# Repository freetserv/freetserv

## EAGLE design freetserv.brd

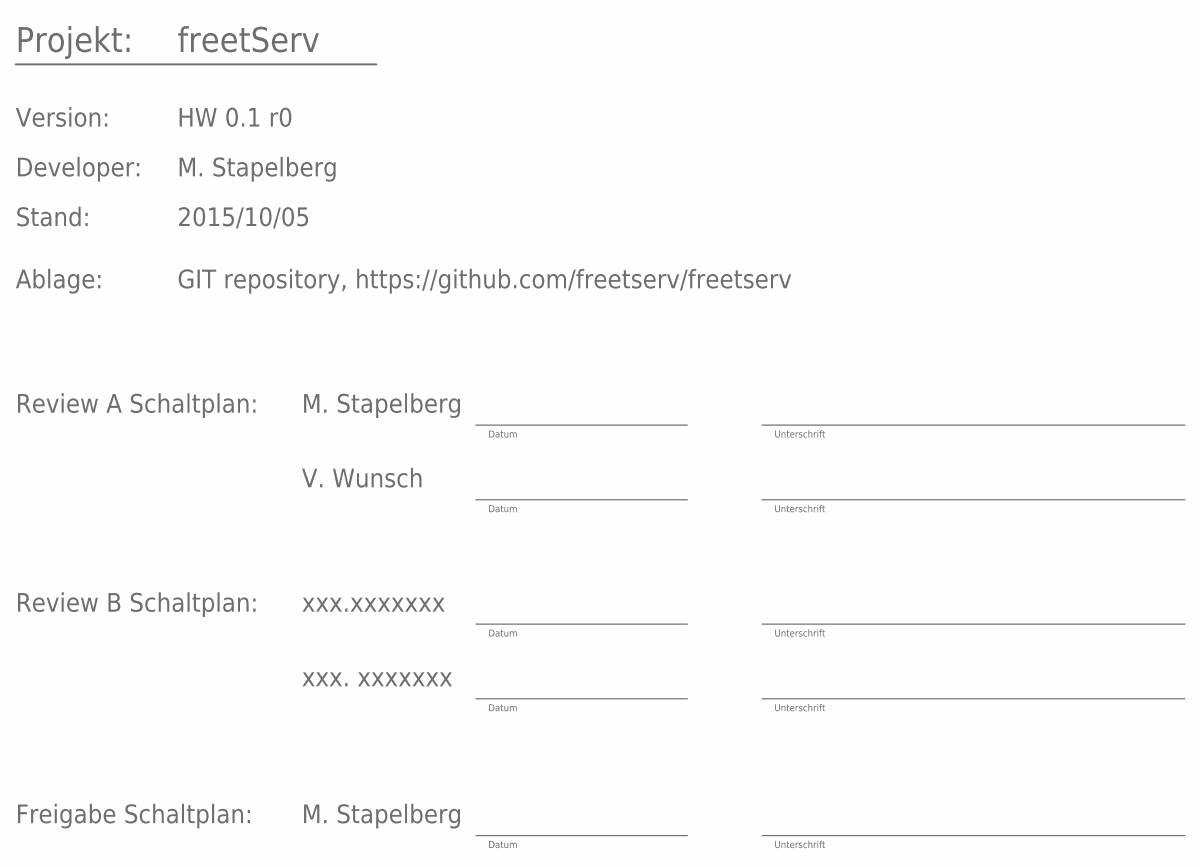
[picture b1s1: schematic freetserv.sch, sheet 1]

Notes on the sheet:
freetServ
Projekt:
Version:
HW 0.1 r0
Developer:
M. Stapelberg
Stand:
2015/10/05
Review A Schaltplan:
Datum
Unterschrift
V. Wunsch
Freigabe Schaltplan:
Ablage:
GIT repository, https://github.com/freetserv/freetserv
Review B Schaltplan:
xxx.xxxxxxx
xxx. xxxxxxx

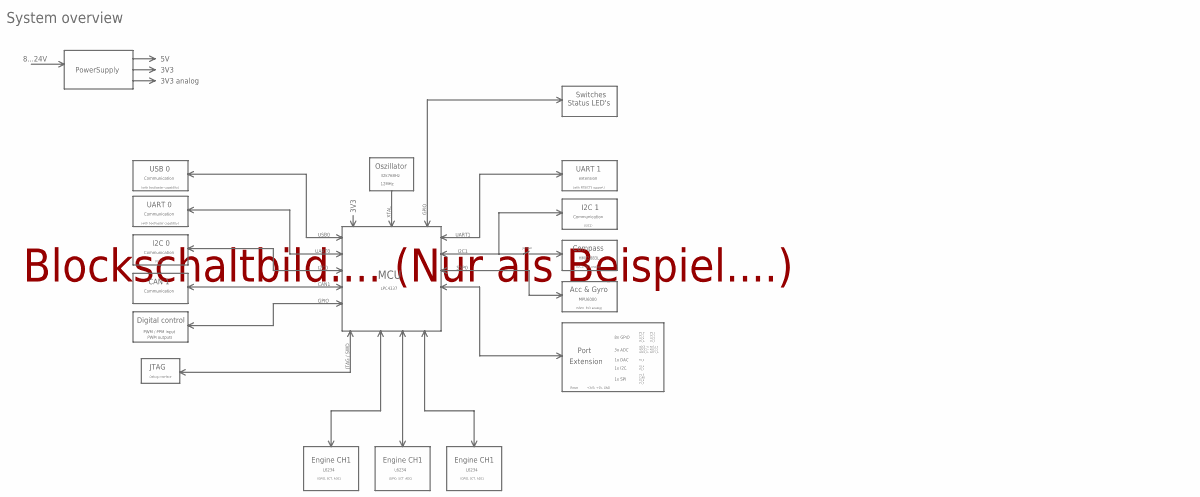
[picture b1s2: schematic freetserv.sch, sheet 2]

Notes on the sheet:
System overview
MCU
PowerSupply
3V3
3V3 analog
8...24V
JTAG
PWM / PPM input
PWM outputs
Digital control
Communication
CAN 1
I2C 0
UART 0
USB 0
(with bootloader capability)
Debug interface
I2C 1
UART 1
extension
(with RTS/CTS support)
8x GPIO
Port
Extension
3x ADC
1x DAC
1x I2C
1x SPI
Reset
+3V3, +5V, GND
(I2C0)
HMC5883L
Compass
Jumper
I2C1
UART1
UART0
USB0
I2C0
(I2C1)

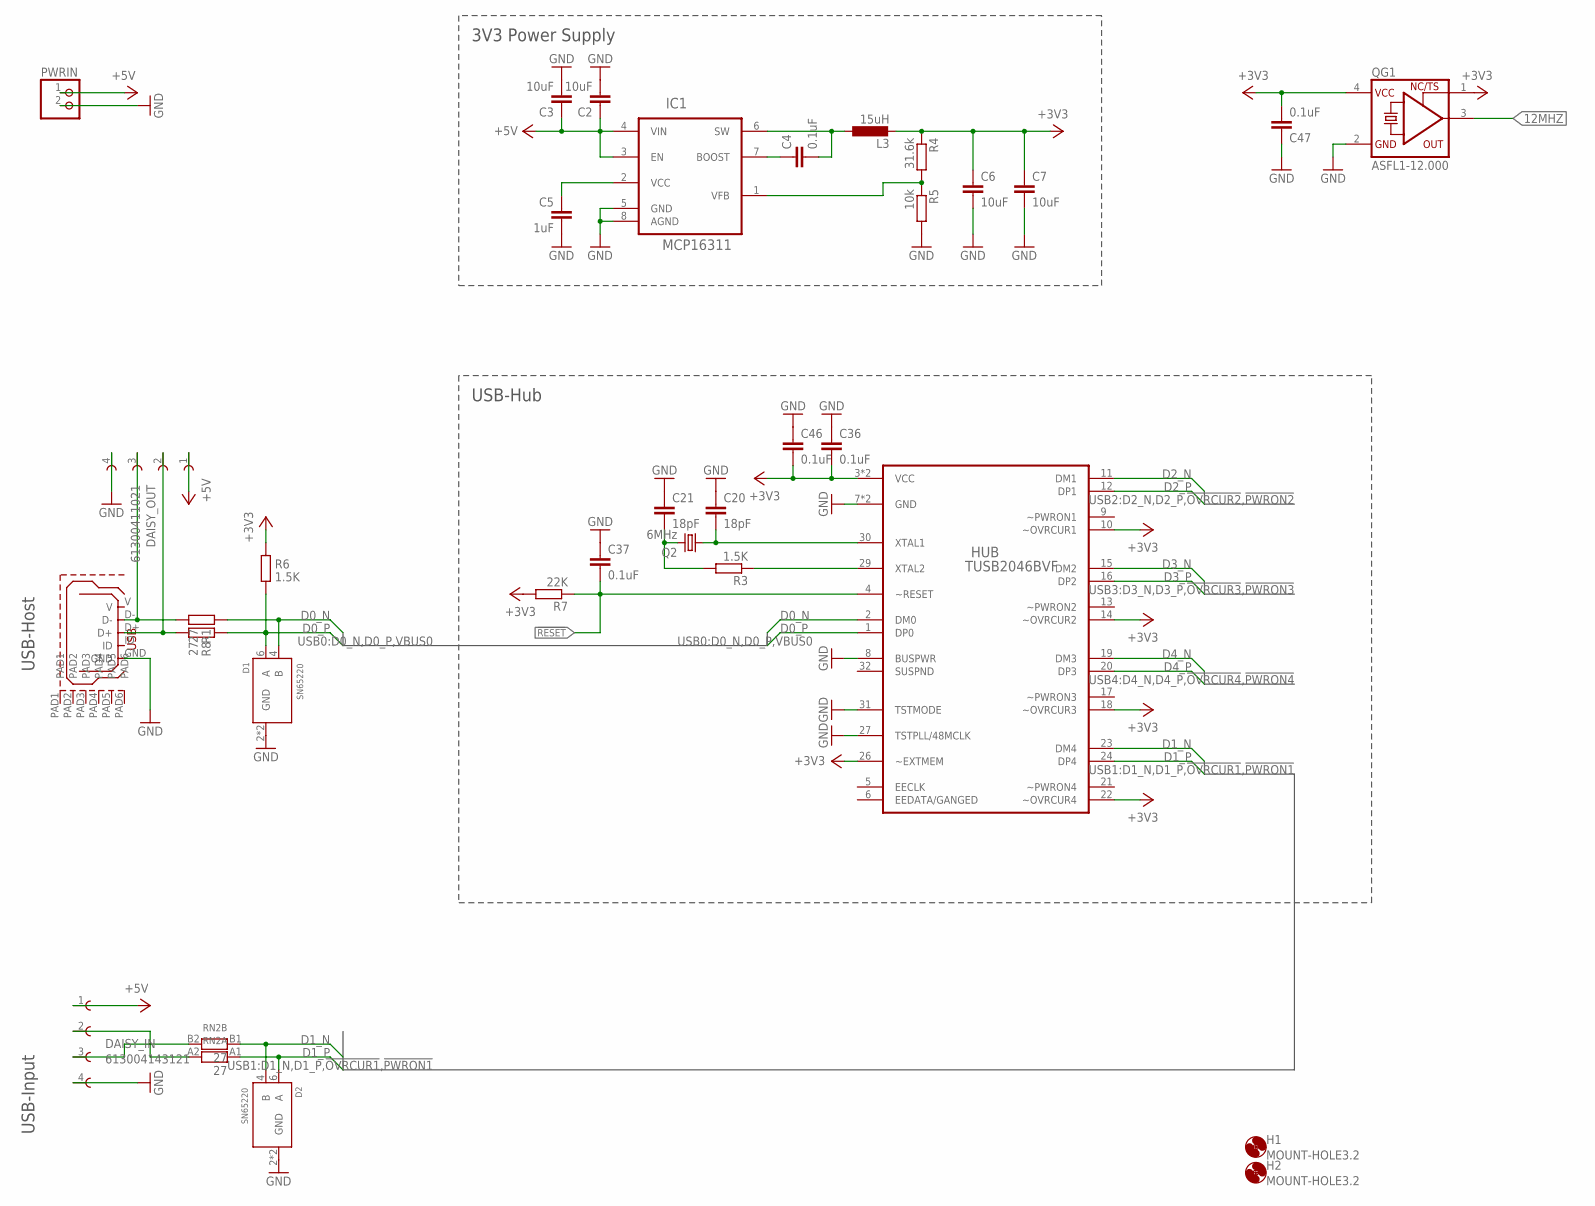
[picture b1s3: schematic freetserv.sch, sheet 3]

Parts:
C2, C3, C6, C7: 10uF; C0805; PARTNO 490-10517-1-ND
C4, C36, C37, C46, C47: 0.1uF; C0805; PARTNO 1276-1003-1-ND
C5: 1uF; C0805; PARTNO 311-1365-1-ND
C20, C21: 18pF; C0805; PARTNO 709-1171-1-ND
D1, D2: SN65220; SOT23-6; PARTNO 296-9694-1-ND
DAISY_IN: 613004143121; PARTNO 732-2863-ND
DAISY_OUT: 61300411021; PARTNO 732-5337-ND
H1, H2: MOUNT-HOLE3.2; 3,2
HUB: TUSB2046BVF; QFP80P900X900X145-32N
IC1: MCP16311; MSOP8; PARTNO MCP16311-E/MS-ND
L3: 15uH; NR60XX; PARTNO 587-2624-1-ND
PWRIN: PINHD-1X2; 1X02; PARTNO A1921-ND
Q2: 6MHz; CSM-7X-DU; PARTNO 535-10208-1-ND
QG1: ASFL1-12.000; XO53; PARTNO 535-9253-1-ND
R1, R8: 27; R0805; PARTNO 311-27ARCT-ND
R3, R6: 1.5K; R0805; PARTNO 311-1.5KARCT-ND
R4: 31.6k; R0805; PARTNO 311-31.6KCRCT-ND
R5: 10k; R0805; PARTNO 311-10KARCT-ND
R7: 22K; R0805; PARTNO 311-22KARCT-ND
RN2: 27; EXBV4V; PARTNO Y2270CT-ND
USB_HOST: USB_MICROB; USB_MICROB_PACKAGE; PARTNO H11634CT-ND

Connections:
12MHZ: QG1.3 (OUT); also elsewhere on the board
!RESET: C37.2, HUB.4 (~RESET), R7.1; also elsewhere on the board
+3V3: C6.1, C7.1, C36.2, C46.2, C47.2, HUB.3 (VCC), HUB.10 (~OVRCUR1), HUB.14 (~OVRCUR2), HUB.18 (~OVRCUR3), HUB.22 (~OVRCUR4), HUB.25 (VCC), HUB.26 (~EXTMEM), L3.2, QG1.1 (TS), QG1.4 (VCC), R4.1, R6.1, R7.2; also elsewhere on the board
+5V: C2.1, C3.1, DAISY_IN.1, DAISY_OUT.1, IC1.3 (EN), IC1.4 (VIN), PWRIN.1
D0_N: D1.4 (B), HUB.2 (DM0), R1.1
D0_P: D1.6 (A), HUB.1 (DP0), R6.2, R8.1
D1_N: D2.4 (B), HUB.23 (DM4), RN2.B1 (1)
D1_P: D2.6 (A), HUB.24 (DP4), RN2.A1 (1)
D2_N: HUB.11 (DM1); also elsewhere on the board
D2_P: HUB.12 (DP1); also elsewhere on the board
D3_N: HUB.15 (DM2); also elsewhere on the board
D3_P: HUB.16 (DP2); also elsewhere on the board
D4_N: HUB.19 (DM3); also elsewhere on the board
D4_P: HUB.20 (DP3); also elsewhere on the board
DX0_N: DAISY_OUT.3, R1.2, USB_HOST.D-
DX0_P: DAISY_OUT.2, R8.2, USB_HOST.D+
GND: C2.2, C3.2, C5.2, C6.2, C7.2, C20.1, C21.1, C36.1, C37.1, C46.1, C47.1, D1.2 (GND), D1.5 (GND), D2.2 (GND), D2.5 (GND), DAISY_IN.4, DAISY_OUT.4, HUB.7 (GND), HUB.8 (BUSPWR), HUB.27 (TSTPLL/48MCLK), HUB.28 (GND), HUB.31 (TSTMODE), IC1.5 (GND), IC1.8 (AGND), PWRIN.2, QG1.2 (GND), R5.2, USB_HOST.GND; also elsewhere on the board
unnamed: C4.1, IC1.7 (BOOST)
unnamed: C4.2, IC1.6 (SW), L3.1
unnamed: IC1.1 (VFB), R4.2, R5.1
unnamed: DAISY_IN.2, RN2.A2 (2)
unnamed: DAISY_IN.3, RN2.B2 (2)
unnamed: C5.1, IC1.2 (VCC)
unnamed: HUB.29 (XTAL2), R3.1
unnamed: C20.2, HUB.30 (XTAL1), Q2.1
unnamed: C21.2, Q2.2, R3.2

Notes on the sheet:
3V3 Power Supply
USB-Hub
USB-Input
USB-Host

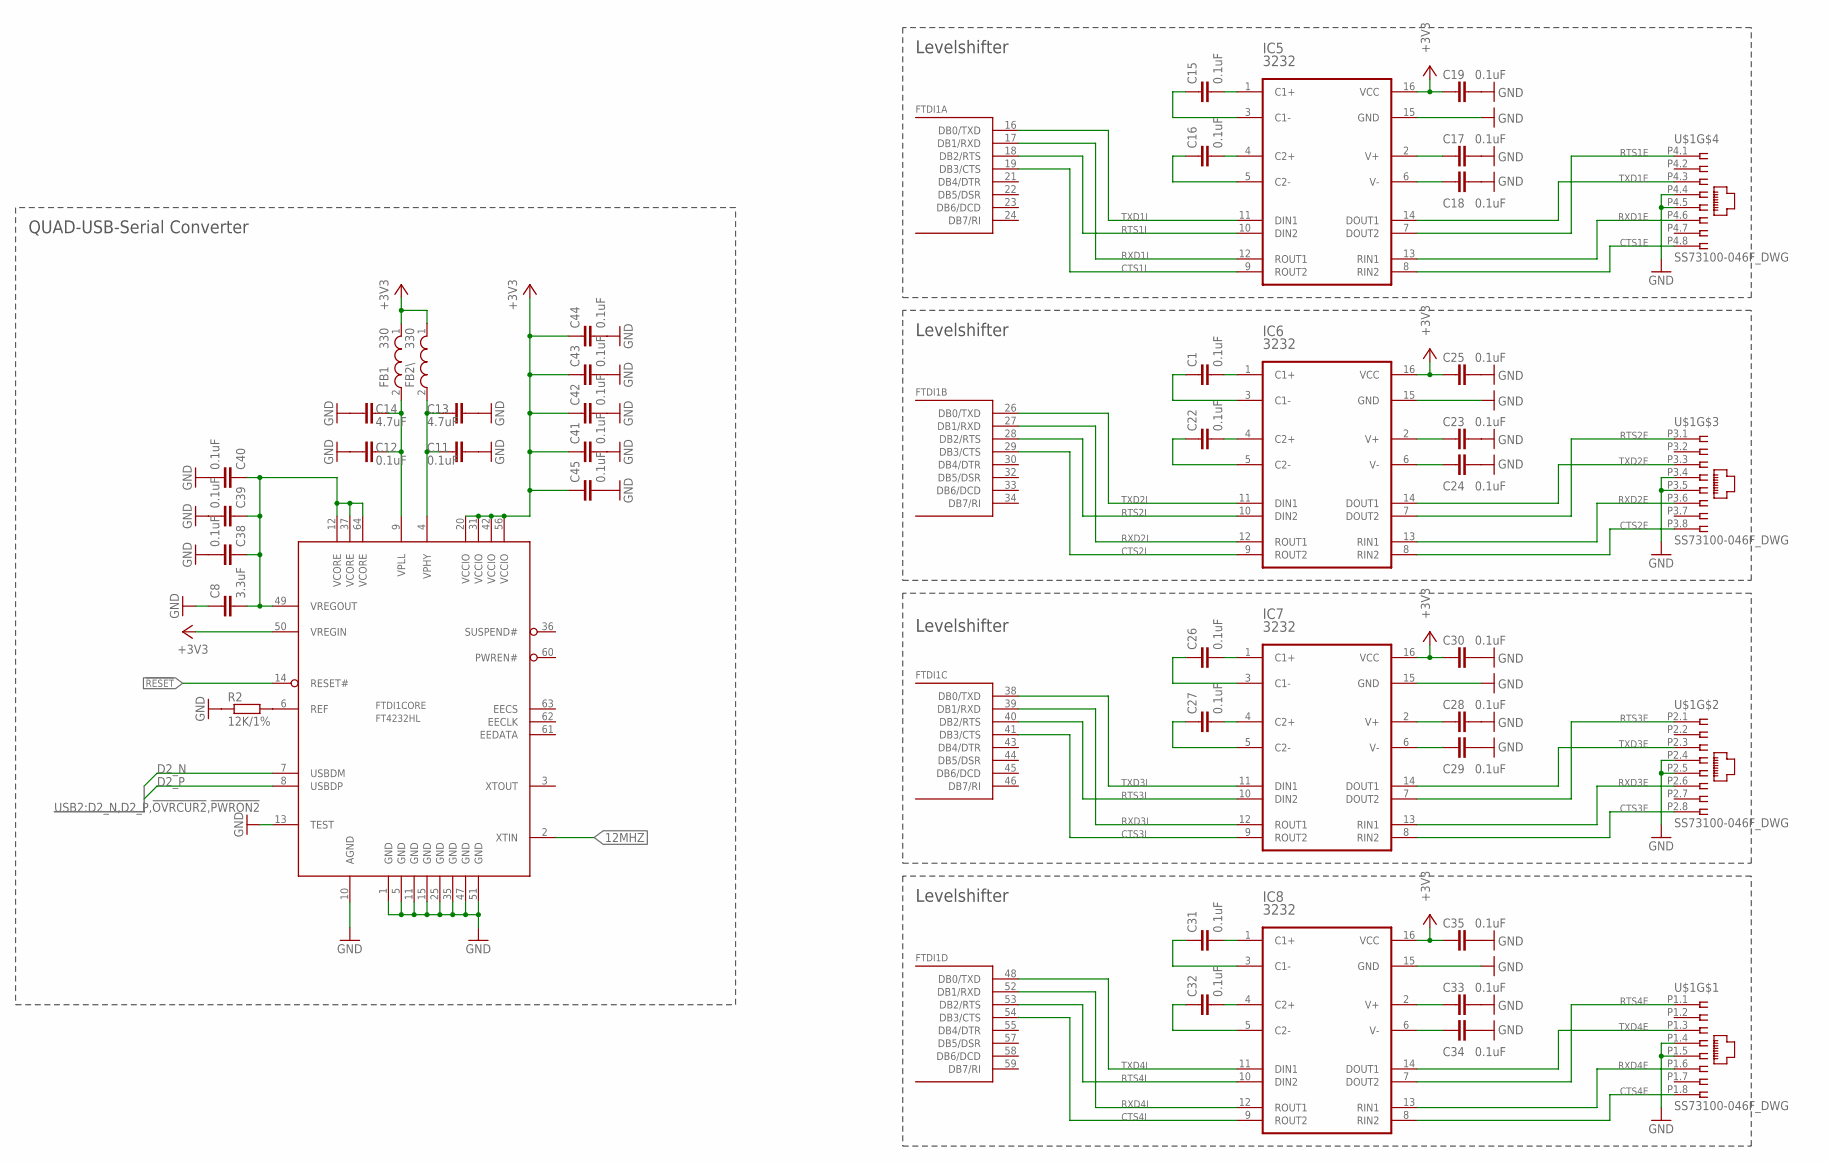
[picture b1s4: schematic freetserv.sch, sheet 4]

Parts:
C1, C11, C12, C15, C16, C17, C18, C19, C22, C23, C24, C25, C26, C27, C28, C29, C30, C31, C32, C33, C34, C35, C38, C39, C40, C41, C42, C43, C44, C45: 0.1uF; C0805; PARTNO 1276-1003-1-ND
C8: 3.3uF; C0805; PARTNO 445-7589-1-ND
C13, C14: 4.7uF; C0805; PARTNO 1276-2972-1-ND
FB1, FB2\: 330; WE-KI_0805A; PARTNO 490-5988-1-ND
FTDI1: FT4232HL; LQFP64; PARTNO 768-1026-1-ND
IC5, IC6, IC7, IC8: 3232; SOP65P640X120-16N; PARTNO 296-19263-1-ND
R2: 12K/1%; R0805; PARTNO 311-12.0KCRCT-ND
U$1: SS73100-046F_DWG; SS73100-046F; PARTNO 380-1225-ND

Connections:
12MHZ: FTDI1.2 (XTIN); also elsewhere on the board
!RESET: FTDI1.14 (RESET#); also elsewhere on the board
+1V8-1: C8.2, C38.1, C39.1, C40.1, FTDI1.12 (VCORE), FTDI1.37 (VCORE), FTDI1.49 (VREGOUT), FTDI1.64 (VCORE)
+3V3: C19.2, C25.2, C30.2, C35.2, C41.1, C42.1, C43.1, C44.1, C45.1, FB1.1, FB2\.1, FTDI1.20 (VCCIO), FTDI1.31 (VCCIO), FTDI1.42 (VCCIO), FTDI1.50 (VREGIN), FTDI1.56 (VCCIO), IC5.16 (VCC), IC6.16 (VCC), IC7.16 (VCC), IC8.16 (VCC); also elsewhere on the board
CTS1E: IC5.8 (RIN2), U$1.P4.8 (8)
CTS1I: FTDI1.19 (DB3/CTS), IC5.9 (ROUT2)
CTS2E: IC6.8 (RIN2), U$1.P3.8 (8)
CTS2I: FTDI1.29 (DB3/CTS), IC6.9 (ROUT2)
CTS3E: IC7.8 (RIN2), U$1.P2.8 (8)
CTS3I: FTDI1.41 (DB3/CTS), IC7.9 (ROUT2)
CTS4E: IC8.8 (RIN2), U$1.P1.8 (8)
CTS4I: FTDI1.54 (DB3/CTS), IC8.9 (ROUT2)
D2_N: FTDI1.7 (USBDM); also elsewhere on the board
D2_P: FTDI1.8 (USBDP); also elsewhere on the board
GND: C8.1, C11.2, C12.2, C13.2, C14.2, C17.1, C18.1, C19.1, C23.1, C24.1, C25.1, C28.1, C29.1, C30.1, C33.1, C34.1, C35.1, C38.2, C39.2, C40.2, C41.2, C42.2, C43.2, C44.2, C45.2, FTDI1.1 (GND), FTDI1.5 (GND), FTDI1.10 (AGND), FTDI1.11 (GND), FTDI1.13 (TEST), FTDI1.15 (GND), FTDI1.25 (GND), FTDI1.35 (GND), FTDI1.47 (GND), FTDI1.51 (GND), IC5.15 (GND), IC6.15 (GND), IC7.15 (GND), IC8.15 (GND), R2.1, U$1.P1.4 (4), U$1.P1.5 (5), U$1.P2.4 (4), U$1.P2.5 (5), U$1.P3.4 (4), U$1.P3.5 (5), U$1.P4.4 (4), U$1.P4.5 (5); also elsewhere on the board
unnamed: C1.2, IC6.1 (C1+)
unnamed: C1.1, IC6.3 (C1-)
unnamed: C22.2, IC6.4 (C2+)
unnamed: C22.1, IC6.5 (C2-)
unnamed: FTDI1.6 (REF), R2.2
unnamed: C11.1, C13.1, FB2\.2, FTDI1.4 (VPHY)
unnamed: C12.1, C14.1, FB1.2, FTDI1.9 (VPLL)
unnamed: C23.2, IC6.2 (V+)
unnamed: C24.2, IC6.6 (V-)
unnamed: C15.2, IC5.1 (C1+)
unnamed: C15.1, IC5.3 (C1-)
unnamed: C16.2, IC5.4 (C2+)
unnamed: C16.1, IC5.5 (C2-)
unnamed: C17.2, IC5.2 (V+)
unnamed: C18.2, IC5.6 (V-)
unnamed: C26.2, IC7.1 (C1+)
unnamed: C26.1, IC7.3 (C1-)
unnamed: C27.2, IC7.4 (C2+)
unnamed: C27.1, IC7.5 (C2-)
unnamed: C28.2, IC7.2 (V+)
unnamed: C29.2, IC7.6 (V-)
unnamed: C31.2, IC8.1 (C1+)
unnamed: C31.1, IC8.3 (C1-)
unnamed: C32.2, IC8.4 (C2+)
unnamed: C32.1, IC8.5 (C2-)
unnamed: C33.2, IC8.2 (V+)
unnamed: C34.2, IC8.6 (V-)
RTS1E: IC5.7 (DOUT2), U$1.P4.1 (1)
RTS1I: FTDI1.18 (DB2/RTS), IC5.10 (DIN2)
RTS2E: IC6.7 (DOUT2), U$1.P3.1 (1)
RTS2I: FTDI1.28 (DB2/RTS), IC6.10 (DIN2)
RTS3E: IC7.7 (DOUT2), U$1.P2.1 (1)
RTS3I: FTDI1.40 (DB2/RTS), IC7.10 (DIN2)
RTS4E: IC8.7 (DOUT2), U$1.P1.1 (1)
RTS4I: FTDI1.53 (DB2/RTS), IC8.10 (DIN2)
RXD1E: IC5.13 (RIN1), U$1.P4.6 (6)
RXD1I: FTDI1.17 (DB1/RXD), IC5.12 (ROUT1)
RXD2E: IC6.13 (RIN1), U$1.P3.6 (6)
RXD2I: FTDI1.27 (DB1/RXD), IC6.12 (ROUT1)
RXD3E: IC7.13 (RIN1), U$1.P2.6 (6)
RXD3I: FTDI1.39 (DB1/RXD), IC7.12 (ROUT1)
RXD4E: IC8.13 (RIN1), U$1.P1.6 (6)
RXD4I: FTDI1.52 (DB1/RXD), IC8.12 (ROUT1)
TXD1E: IC5.14 (DOUT1), U$1.P4.3 (3)
TXD1I: FTDI1.16 (DB0/TXD), IC5.11 (DIN1)
TXD2E: IC6.14 (DOUT1), U$1.P3.3 (3)
TXD2I: FTDI1.26 (DB0/TXD), IC6.11 (DIN1)
TXD3E: IC7.14 (DOUT1), U$1.P2.3 (3)
TXD3I: FTDI1.38 (DB0/TXD), IC7.11 (DIN1)
TXD4E: IC8.14 (DOUT1), U$1.P1.3 (3)
TXD4I: FTDI1.48 (DB0/TXD), IC8.11 (DIN1)

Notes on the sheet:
Levelshifter
QUAD-USB-Serial Converter

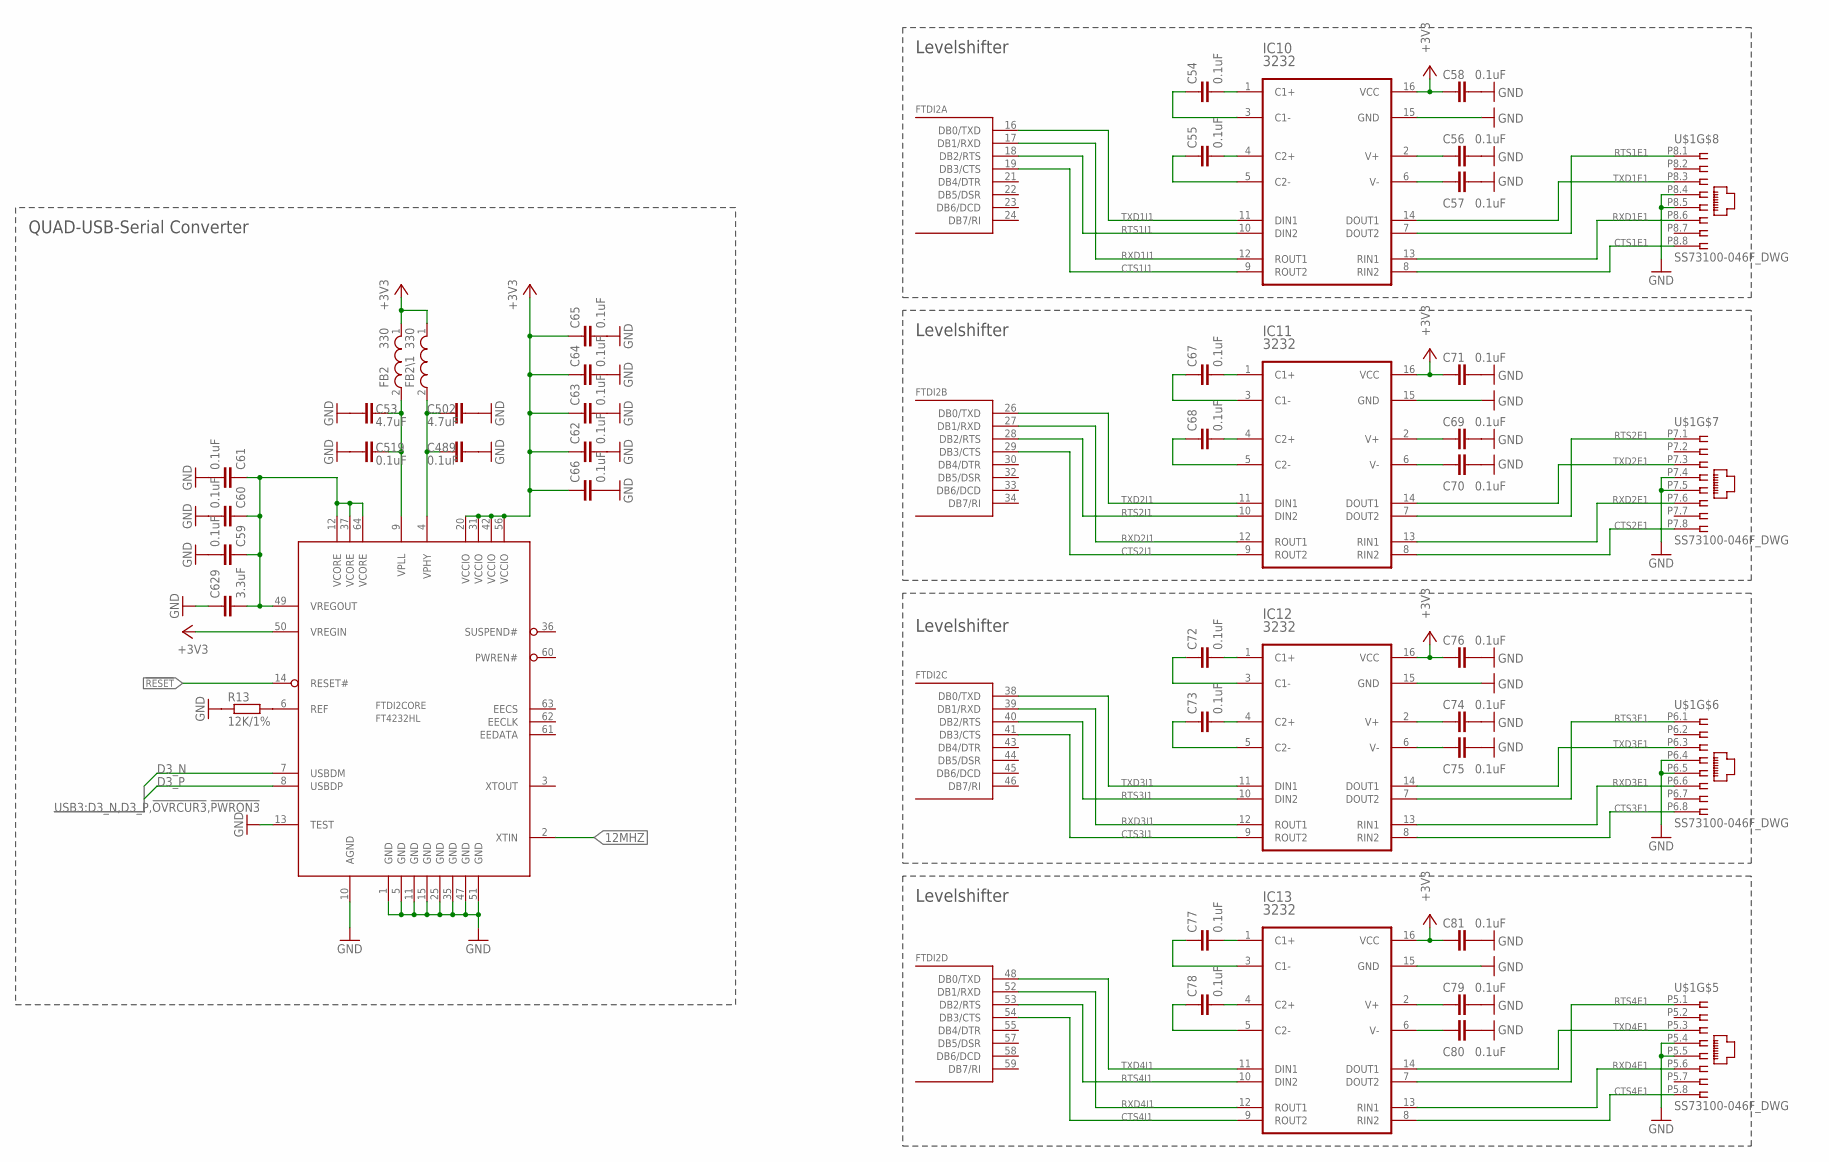
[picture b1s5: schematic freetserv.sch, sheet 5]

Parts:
C53, C502: 4.7uF; C0805; PARTNO 1276-2972-1-ND
C54, C55, C56, C57, C58, C59, C60, C61, C62, C63, C64, C65, C66, C67, C68, C69, C70, C71, C72, C73, C74, C75, C76, C77, C78, C79, C80, C81, C489, C519: 0.1uF; C0805; PARTNO 1276-1003-1-ND
C629: 3.3uF; C0805; PARTNO 445-7589-1-ND
FB2, FB2\1: 330; WE-KI_0805A; PARTNO 490-5988-1-ND
FTDI2: FT4232HL; LQFP64; PARTNO 768-1026-1-ND
IC10, IC11, IC12, IC13: 3232; SOP65P640X120-16N; PARTNO 296-19263-1-ND
R13: 12K/1%; R0805; PARTNO 311-12.0KCRCT-ND
U$1: SS73100-046F_DWG; SS73100-046F; PARTNO 380-1225-ND

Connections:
12MHZ: FTDI2.2 (XTIN); also elsewhere on the board
!RESET: FTDI2.14 (RESET#); also elsewhere on the board
+1V8-2: C59.1, C60.1, C61.1, C629.2, FTDI2.12 (VCORE), FTDI2.37 (VCORE), FTDI2.49 (VREGOUT), FTDI2.64 (VCORE)
+3V3: C58.2, C62.1, C63.1, C64.1, C65.1, C66.1, C71.2, C76.2, C81.2, FB2.1, FB2\1.1, FTDI2.20 (VCCIO), FTDI2.31 (VCCIO), FTDI2.42 (VCCIO), FTDI2.50 (VREGIN), FTDI2.56 (VCCIO), IC10.16 (VCC), IC11.16 (VCC), IC12.16 (VCC), IC13.16 (VCC); also elsewhere on the board
CTS1E1: IC10.8 (RIN2), U$1.P8.8 (8)
CTS1I1: FTDI2.19 (DB3/CTS), IC10.9 (ROUT2)
CTS2E1: IC11.8 (RIN2), U$1.P7.8 (8)
CTS2I1: FTDI2.29 (DB3/CTS), IC11.9 (ROUT2)
CTS3E1: IC12.8 (RIN2), U$1.P6.8 (8)
CTS3I1: FTDI2.41 (DB3/CTS), IC12.9 (ROUT2)
CTS4E1: IC13.8 (RIN2), U$1.P5.8 (8)
CTS4I1: FTDI2.54 (DB3/CTS), IC13.9 (ROUT2)
D3_N: FTDI2.7 (USBDM); also elsewhere on the board
D3_P: FTDI2.8 (USBDP); also elsewhere on the board
GND: C53.2, C56.1, C57.1, C58.1, C59.2, C60.2, C61.2, C62.2, C63.2, C64.2, C65.2, C66.2, C69.1, C70.1, C71.1, C74.1, C75.1, C76.1, C79.1, C80.1, C81.1, C489.2, C502.2, C519.2, C629.1, FTDI2.1 (GND), FTDI2.5 (GND), FTDI2.10 (AGND), FTDI2.11 (GND), FTDI2.13 (TEST), FTDI2.15 (GND), FTDI2.25 (GND), FTDI2.35 (GND), FTDI2.47 (GND), FTDI2.51 (GND), IC10.15 (GND), IC11.15 (GND), IC12.15 (GND), IC13.15 (GND), R13.1, U$1.P5.4 (4), U$1.P5.5 (5), U$1.P6.4 (4), U$1.P6.5 (5), U$1.P7.4 (4), U$1.P7.5 (5), U$1.P8.4 (4), U$1.P8.5 (5); also elsewhere on the board
unnamed: FTDI2.6 (REF), R13.2
unnamed: C54.2, IC10.1 (C1+)
unnamed: C54.1, IC10.3 (C1-)
unnamed: C55.2, IC10.4 (C2+)
unnamed: C55.1, IC10.5 (C2-)
unnamed: C56.2, IC10.2 (V+)
unnamed: C57.2, IC10.6 (V-)
unnamed: C67.2, IC11.1 (C1+)
unnamed: C67.1, IC11.3 (C1-)
unnamed: C68.2, IC11.4 (C2+)
unnamed: C68.1, IC11.5 (C2-)
unnamed: C69.2, IC11.2 (V+)
unnamed: C70.2, IC11.6 (V-)
unnamed: C72.2, IC12.1 (C1+)
unnamed: C72.1, IC12.3 (C1-)
unnamed: C73.2, IC12.4 (C2+)
unnamed: C73.1, IC12.5 (C2-)
unnamed: C74.2, IC12.2 (V+)
unnamed: C75.2, IC12.6 (V-)
unnamed: C77.1, IC13.3 (C1-)
unnamed: C78.2, IC13.4 (C2+)
unnamed: C78.1, IC13.5 (C2-)
unnamed: C79.2, IC13.2 (V+)
unnamed: C80.2, IC13.6 (V-)
unnamed: C489.1, C502.1, FB2\1.2, FTDI2.4 (VPHY)
unnamed: C53.1, C519.1, FB2.2, FTDI2.9 (VPLL)
unnamed: C77.2, IC13.1 (C1+)
RTS1E1: IC10.7 (DOUT2), U$1.P8.1 (1)
RTS1I1: FTDI2.18 (DB2/RTS), IC10.10 (DIN2)
RTS2E1: IC11.7 (DOUT2), U$1.P7.1 (1)
RTS2I1: FTDI2.28 (DB2/RTS), IC11.10 (DIN2)
RTS3E1: IC12.7 (DOUT2), U$1.P6.1 (1)
RTS3I1: FTDI2.40 (DB2/RTS), IC12.10 (DIN2)
RTS4E1: IC13.7 (DOUT2), U$1.P5.1 (1)
RTS4I1: FTDI2.53 (DB2/RTS), IC13.10 (DIN2)
RXD1E1: IC10.13 (RIN1), U$1.P8.6 (6)
RXD1I1: FTDI2.17 (DB1/RXD), IC10.12 (ROUT1)
RXD2E1: IC11.13 (RIN1), U$1.P7.6 (6)
RXD2I1: FTDI2.27 (DB1/RXD), IC11.12 (ROUT1)
RXD3E1: IC12.13 (RIN1), U$1.P6.6 (6)
RXD3I1: FTDI2.39 (DB1/RXD), IC12.12 (ROUT1)
RXD4E1: IC13.13 (RIN1), U$1.P5.6 (6)
RXD4I1: FTDI2.52 (DB1/RXD), IC13.12 (ROUT1)
TXD1E1: IC10.14 (DOUT1), U$1.P8.3 (3)
TXD1I1: FTDI2.16 (DB0/TXD), IC10.11 (DIN1)
TXD2E1: IC11.14 (DOUT1), U$1.P7.3 (3)
TXD2I1: FTDI2.26 (DB0/TXD), IC11.11 (DIN1)
TXD3E1: IC12.14 (DOUT1), U$1.P6.3 (3)
TXD3I1: FTDI2.38 (DB0/TXD), IC12.11 (DIN1)
TXD4E1: IC13.14 (DOUT1), U$1.P5.3 (3)
TXD4I1: FTDI2.48 (DB0/TXD), IC13.11 (DIN1)

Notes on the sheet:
Levelshifter
QUAD-USB-Serial Converter

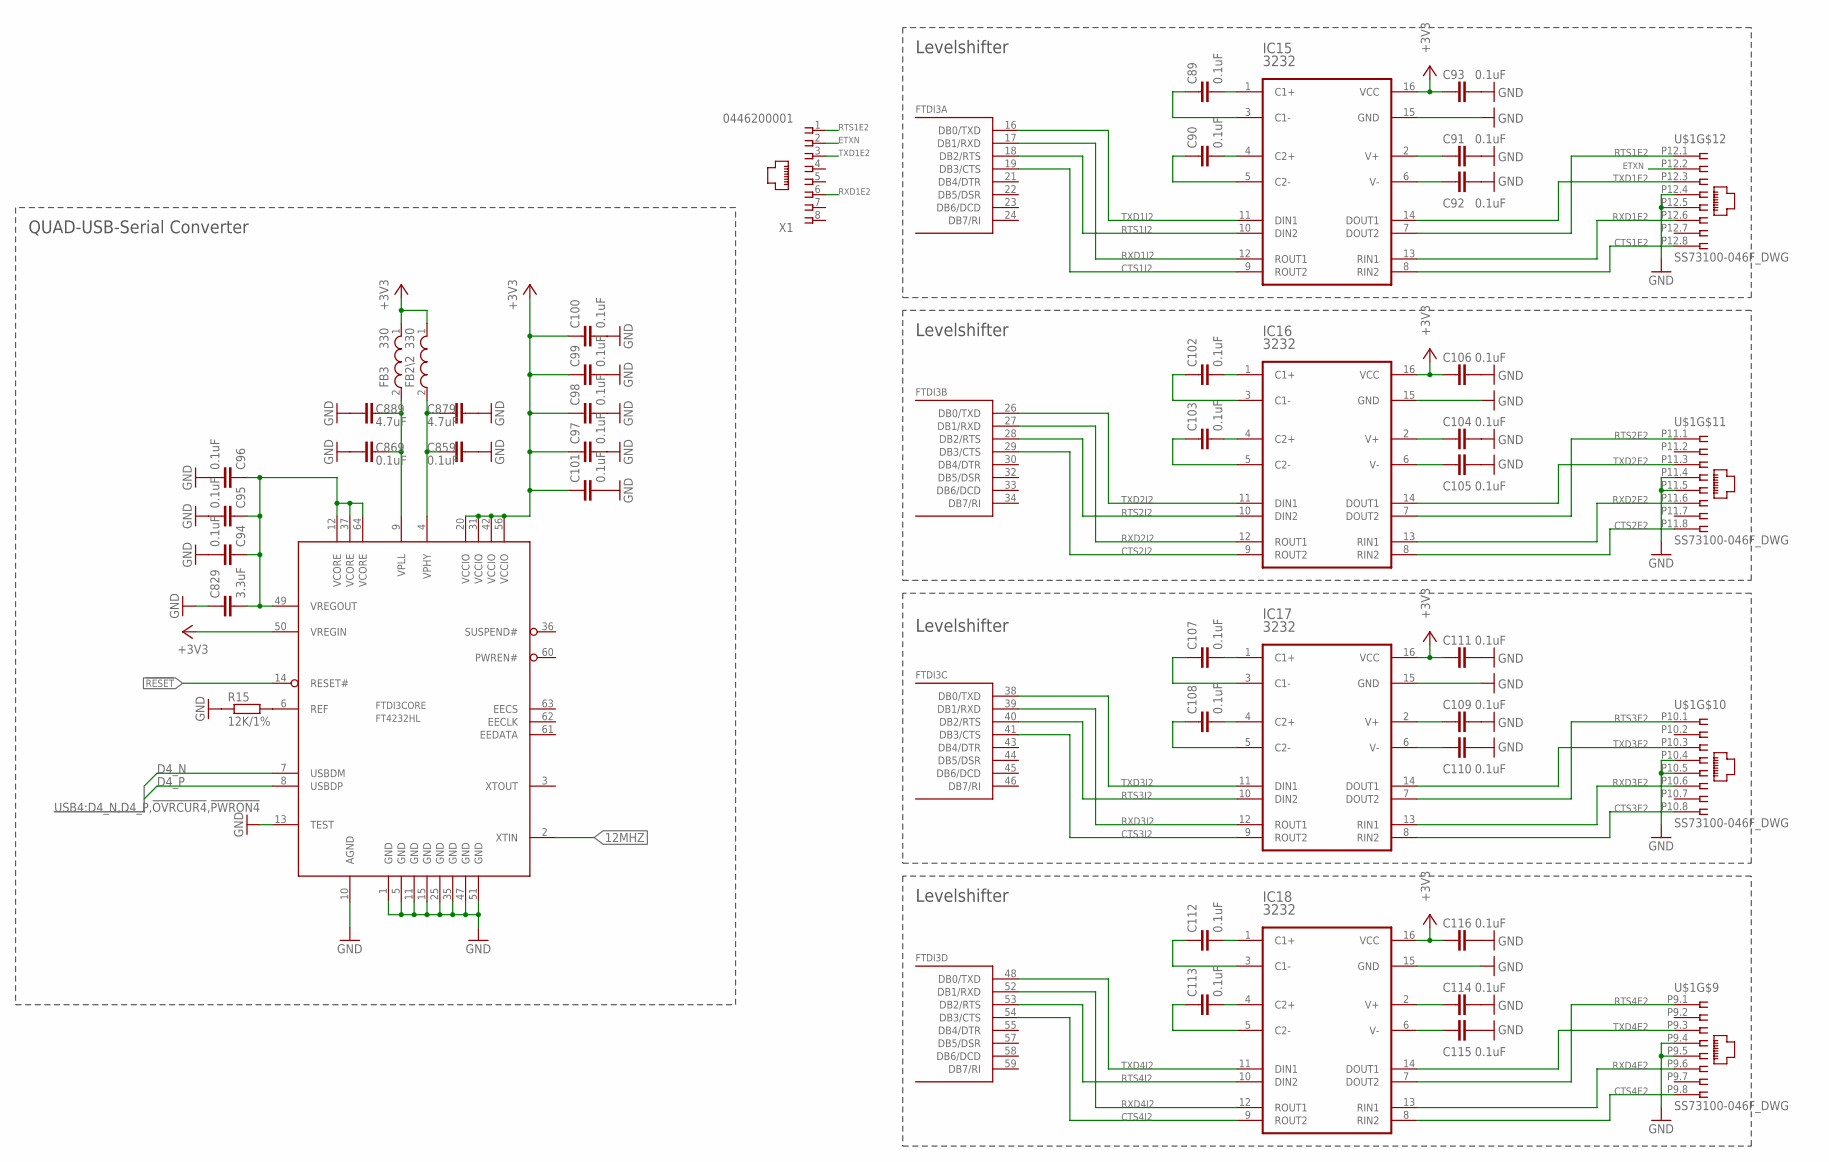
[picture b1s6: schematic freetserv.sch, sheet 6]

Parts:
C89, C90, C91, C92, C93, C94, C95, C96, C97, C98, C99, C100, C101, C102, C103, C104, C105, C106, C107, C108, C109, C110, C111, C112, C113, C114, C115, C116, C859, C869: 0.1uF; C0805; PARTNO 1276-1003-1-ND
C829: 3.3uF; C0805; PARTNO 445-7589-1-ND
C879, C889: 4.7uF; C0805; PARTNO 1276-2972-1-ND
FB2\2, FB3: 330; WE-KI_0805A; PARTNO 490-5988-1-ND
FTDI3: FT4232HL; LQFP64; PARTNO 768-1026-1-ND
IC15, IC16, IC17, IC18: 3232; SOP65P640X120-16N; PARTNO 296-19263-1-ND
R15: 12K/1%; R0805; PARTNO 311-12.0KCRCT-ND
U$1: SS73100-046F_DWG; SS73100-046F; PARTNO 380-1225-ND
X1: 0446200001

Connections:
12MHZ: FTDI3.2 (XTIN); also elsewhere on the board
!RESET: FTDI3.14 (RESET#); also elsewhere on the board
+1V8-3: C94.1, C95.1, C96.1, C829.2, FTDI3.12 (VCORE), FTDI3.37 (VCORE), FTDI3.49 (VREGOUT), FTDI3.64 (VCORE)
+3V3: C93.2, C97.1, C98.1, C99.1, C100.1, C101.1, C106.2, C111.2, C116.2, FB2\2.1, FB3.1, FTDI3.20 (VCCIO), FTDI3.31 (VCCIO), FTDI3.42 (VCCIO), FTDI3.50 (VREGIN), FTDI3.56 (VCCIO), IC15.16 (VCC), IC16.16 (VCC), IC17.16 (VCC), IC18.16 (VCC); also elsewhere on the board
CTS1E2: IC15.8 (RIN2), U$1.P12.8 (8)
CTS1I2: FTDI3.19 (DB3/CTS), IC15.9 (ROUT2)
CTS2E2: IC16.8 (RIN2), U$1.P11.8 (8)
CTS2I2: FTDI3.29 (DB3/CTS), IC16.9 (ROUT2)
CTS3E2: IC17.8 (RIN2), U$1.P10.8 (8)
CTS3I2: FTDI3.41 (DB3/CTS), IC17.9 (ROUT2)
CTS4E2: IC18.8 (RIN2), U$1.P9.8 (8)
CTS4I2: FTDI3.54 (DB3/CTS), IC18.9 (ROUT2)
D4_N: FTDI3.7 (USBDM); also elsewhere on the board
D4_P: FTDI3.8 (USBDP); also elsewhere on the board
ETXN: U$1.P12.2 (2), X1.2 (7)
GND: C91.1, C92.1, C93.1, C94.2, C95.2, C96.2, C97.2, C98.2, C99.2, C100.2, C101.2, C104.1, C105.1, C106.1, C109.1, C110.1, C111.1, C114.1, C115.1, C116.1, C829.1, C859.2, C869.2, C879.2, C889.2, FTDI3.1 (GND), FTDI3.5 (GND), FTDI3.10 (AGND), FTDI3.11 (GND), FTDI3.13 (TEST), FTDI3.15 (GND), FTDI3.25 (GND), FTDI3.35 (GND), FTDI3.47 (GND), FTDI3.51 (GND), IC15.15 (GND), IC16.15 (GND), IC17.15 (GND), IC18.15 (GND), R15.1, U$1.P9.4 (4), U$1.P9.5 (5), U$1.P10.4 (4), U$1.P10.5 (5), U$1.P11.4 (4), U$1.P11.5 (5), U$1.P12.4 (4), U$1.P12.5 (5); also elsewhere on the board
unnamed: FTDI3.6 (REF), R15.2
unnamed: C859.1, C879.1, FB2\2.2, FTDI3.4 (VPHY)
unnamed: C869.1, C889.1, FB3.2, FTDI3.9 (VPLL)
unnamed: C89.2, IC15.1 (C1+)
unnamed: C89.1, IC15.3 (C1-)
unnamed: C90.2, IC15.4 (C2+)
unnamed: C90.1, IC15.5 (C2-)
unnamed: C91.2, IC15.2 (V+)
unnamed: C92.2, IC15.6 (V-)
unnamed: C102.2, IC16.1 (C1+)
unnamed: C102.1, IC16.3 (C1-)
unnamed: C103.2, IC16.4 (C2+)
unnamed: C103.1, IC16.5 (C2-)
unnamed: C104.2, IC16.2 (V+)
unnamed: C105.2, IC16.6 (V-)
unnamed: C107.2, IC17.1 (C1+)
unnamed: C107.1, IC17.3 (C1-)
unnamed: C108.2, IC17.4 (C2+)
unnamed: C108.1, IC17.5 (C2-)
unnamed: C109.2, IC17.2 (V+)
unnamed: C110.2, IC17.6 (V-)
unnamed: C112.2, IC18.1 (C1+)
unnamed: C112.1, IC18.3 (C1-)
unnamed: C113.2, IC18.4 (C2+)
unnamed: C113.1, IC18.5 (C2-)
unnamed: C114.2, IC18.2 (V+)
unnamed: C115.2, IC18.6 (V-)
RTS1E2: IC15.7 (DOUT2), U$1.P12.1 (1), X1.1 (8)
RTS1I2: FTDI3.18 (DB2/RTS), IC15.10 (DIN2)
RTS2E2: IC16.7 (DOUT2), U$1.P11.1 (1)
RTS2I2: FTDI3.28 (DB2/RTS), IC16.10 (DIN2)
RTS3E2: IC17.7 (DOUT2), U$1.P10.1 (1)
RTS3I2: FTDI3.40 (DB2/RTS), IC17.10 (DIN2)
RTS4E2: IC18.7 (DOUT2), U$1.P9.1 (1)
RTS4I2: FTDI3.53 (DB2/RTS), IC18.10 (DIN2)
RXD1E2: IC15.13 (RIN1), U$1.P12.6 (6), X1.6 (3)
RXD1I2: FTDI3.17 (DB1/RXD), IC15.12 (ROUT1)
RXD2E2: IC16.13 (RIN1), U$1.P11.6 (6)
RXD2I2: FTDI3.27 (DB1/RXD), IC16.12 (ROUT1)
RXD3E2: IC17.13 (RIN1), U$1.P10.6 (6)
RXD3I2: FTDI3.39 (DB1/RXD), IC17.12 (ROUT1)
RXD4E2: IC18.13 (RIN1), U$1.P9.6 (6)
RXD4I2: FTDI3.52 (DB1/RXD), IC18.12 (ROUT1)
TXD1E2: IC15.14 (DOUT1), U$1.P12.3 (3), X1.3 (6)
TXD1I2: FTDI3.16 (DB0/TXD), IC15.11 (DIN1)
TXD2E2: IC16.14 (DOUT1), U$1.P11.3 (3)
TXD2I2: FTDI3.26 (DB0/TXD), IC16.11 (DIN1)
TXD3E2: IC17.14 (DOUT1), U$1.P10.3 (3)
TXD3I2: FTDI3.38 (DB0/TXD), IC17.11 (DIN1)
TXD4E2: IC18.14 (DOUT1), U$1.P9.3 (3)
TXD4I2: FTDI3.48 (DB0/TXD), IC18.11 (DIN1)

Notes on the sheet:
Levelshifter
QUAD-USB-Serial Converter

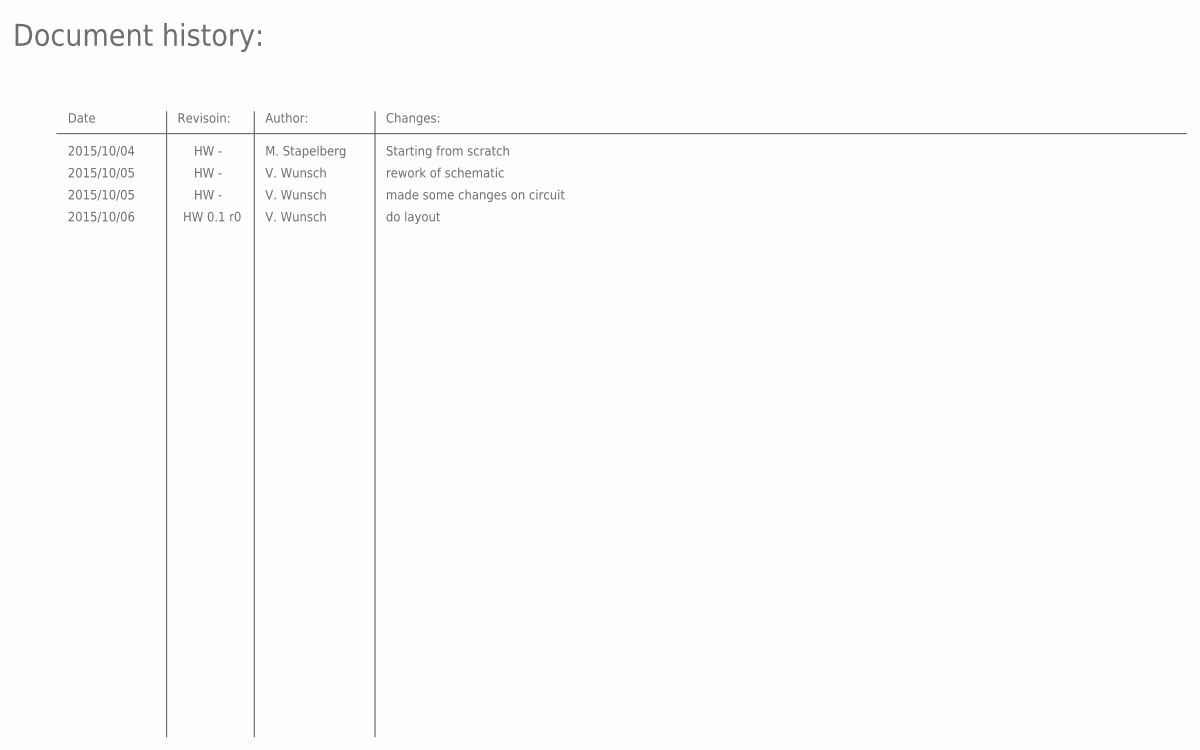
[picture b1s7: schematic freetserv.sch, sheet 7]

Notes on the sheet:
Revisoin:
Document history:
Date
Author:
2015/10/05
2015/10/04
HW -
Changes:
M. Stapelberg
V. Wunsch
Starting from scratch
rework of schematic
made some changes on circuit
do layout
2015/10/06
HW 0.1 r0

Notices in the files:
parts and their libraries:
Wurth_Elektronik_Passive_rev15d: Copyright: Würth Elektronik
